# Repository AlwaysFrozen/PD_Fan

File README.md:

# PD_Fan
A USB TYPE_C powered 4-PIN PWM fan controller  
PD decoy was performed with WCH CH224  
Support 5v, 9v, 12v, 15v, 20v fixed pd gear  
Use the WCH CH571 for BLE communication,PWM control and speed measurement

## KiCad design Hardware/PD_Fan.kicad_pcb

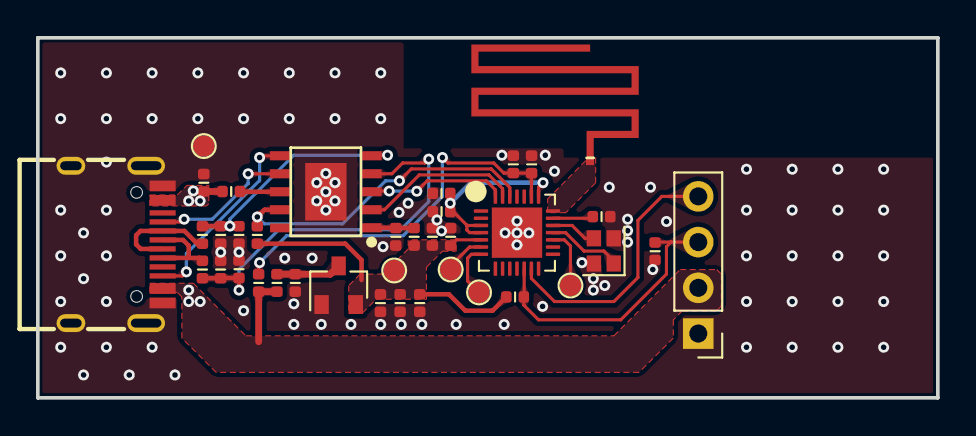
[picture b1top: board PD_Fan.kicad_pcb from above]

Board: 2 copper layers, 50.0 x 20.0 mm, 38 parts (0 on the bottom side), 26 nets.

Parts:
ANT1: Antenna; ANT_AN5129
C1, C2, C4, C5: 10pF/50V; C_0402
C3: 10uF/50V; C_0402
C6, C7: 10uF/6.3V; C_0402
C8, C15: 0.1uF/50V; C_0402
C9: 1uF/10V X7R; C_0402
C10, C11, C13, C14: 2.2uF/6.3V; C_0402
C12: 0.1uF/25V; C_0402
D1, D2: ESD0402TS050D03; C_0402
J1: Conn_01x04_Pin; PinHeader_1x04_P2.54mm_Vertical
J2: TYPE-C; YH-036-013A
R1: 100K; R_0402
R2, R6, R7, R8: 10K; R_0402
R3, R4, R5: 10R; R_0402
R9: 47R; R_0402
TP1: 3.3V; TestPoint_1.2mm
TP2: GND; TestPoint_1.2mm
TP3: RX; TestPoint_1.2mm
TP4: TX; TestPoint_1.2mm
TP5: BOOT; TestPoint_1.2mm
U1: ME6203A33M3G; SOT-23
U2: CH224K; ESSOP10
U3: CH571F; QFN-28-1EP_4x4mm_P0.4mm_EP2.8x2.8mm
Y1: 32MHz; Crystal_SMD_2016-4Pin_2.0x1.6mm

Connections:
3.3V: C6.2, C7.2, C8.2, C10.2, C12.2, R6.1, R8.1, R9.1, TP1.1, U1.2 (VOUT), U3.5 (VIO33/VDD3)
/ANT: ANT1.1 (A), U3.21 (ANT)
/C-USBDM: C5.2, D2.2 (A2), R5.2, U2.5 (DM)
/C-USBDP: C4.1, D1.1 (A1), R4.2, U2.4 (DP)
/CFG1: R8.2, U2.9 (CFG1), U3.26 (PA14/MOSI/TXD0_/AIN4)
/CFG2: U2.2 (CFG2), U3.27 (PA13/SCK0/AIN3)
/CFG3: U2.3 (CFG3), U3.28 (PA12/SCS/AIN2)
/Control: J1.4, U3.13 (PB10/UD-/TMR1_)
/Sense: C15.2, J1.3, R6.2, U3.12 (PB11/UD+/TMR2_)
/VIN_DET: C2.2, R1.2, R2.1, U3.23 (PA4/AIN0)
GND: C1.1, C2.1, C3.1, C4.2, C5.1, C6.1, C7.1, C8.1, C9.1, C10.1, C11.1, C12.1, C13.1, C14.1, C15.1, D1.2 (A2), D2.1 (A1), J1.1, J2.A1 (GND), J2.A12 (GND), J2.B1 (GND), J2.B12 (GND), J2.S1 (SHIELD), R2.2, TP2.1, U1.1 (VSS), U2.11 (GND), U3.29 (GND), Y1.2, Y1.4
unnamed: J2.A5 (CC1), U2.7 (CC1)
unnamed: J2.B5 (CC2), U2.6 (CC2)
unnamed: J2.A6 (D+), J2.B6 (D+), R4.1
unnamed: J2.A7 (D-), J2.B7 (D-), R5.1
unnamed: C3.2, R3.2, U1.3 (VIN)
unnamed: R7.1, U2.8 (VBUS)
unnamed: C9.2, R9.2, U2.1 (VDD)
unnamed: TP3.1, U3.6 (PA8/RXD1)
unnamed: TP4.1, U3.7 (PA9/TMR0/TXD1)
unnamed: TP5.1, U3.17 (PB22/TMR3)
unnamed: C13.2, C14.2, U3.3 (VDCID), U3.4 (VSW), U3.22 (VDCIA)
unnamed: C11.2, U3.20 (VINTA)
unnamed: U3.19 (X32MI), Y1.3
unnamed: U3.18 (X32MO), Y1.1
USB-VIN: C1.2, J1.2, J2.A4 (VBUS), J2.A9 (VBUS), J2.B4 (VBUS), J2.B9 (VBUS), R1.1, R3.1, R7.2

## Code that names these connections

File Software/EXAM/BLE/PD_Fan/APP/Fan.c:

#include "CONFIG.h"
#include "Fan.h"

/*
    CH224 voltage set
    CFG1    CFG2    CFG3
    1       -       -       5v
    0       0       0       9v
    0       0       1       12v
    0       1       1       15v
    0       1       0       20v
*/

#define CFG1_PIN    GPIO_Pin_14
#define CFG2_PIN    GPIO_Pin_13
#define CFG3_PIN    GPIO_Pin_12

#define CFG1_H      GPIOA_SetBits(CFG1_PIN)
#define CFG1_L      GPIOA_ResetBits(CFG1_PIN)
#define CFG2_H      GPIOA_SetBits(CFG2_PIN)
#define CFG2_L      GPIOA_ResetBits(CFG2_PIN)
#define CFG3_H      GPIOA_SetBits(CFG3_PIN)
#define CFG3_L      GPIOA_ResetBits(CFG3_PIN)

#define PWM_FREQ    (25000)
#define PWM_CYCLE   (60000000 / PWM_FREQ)

static uint8_t pd_target_vol = 5;
static uint8_t fan_target_duty = 0;
static uint16_t RPM = 0;

void PD_Init(void)
{
    GPIOA_ModeCfg(GPIO_Pin_0,GPIO_ModeIN_Floating);
    ADC_ExtSingleChSampInit( SampleFreq_3_2, ADC_PGA_0 );

    CFG1_H;
    CFG2_L;
    CFG3_L;
    GPIOA_ModeCfg(CFG1_PIN | CFG2_PIN | CFG3_PIN,GPIO_ModeOut_PP_5mA);
}

void Set_PD_Vol(uint8_t vol)
{
    pd_target_vol = vol;

    switch(vol)
    {
        case 5:
            CFG1_H;
            CFG2_L;
            CFG3_L;
            break;

        case 9:
            CFG1_L;
            CFG2_L;
            CFG3_L;
            break;

        case 12:
            CFG1_L;
            CFG2_L;
            CFG3_H;
            break;

        case 15:
            CFG1_L;
            CFG2_H;
            CFG3_H;
            break;

        case 20:
            CFG1_L;
            CFG2_H;
            CFG3_L;
            break;

        default:
            break;
    }
}

uint8_t Get_PD_Vol(void)
{
    return pd_target_vol;
}

uint16_t Get_VBUS_Vol(void)
{
    uint16_t adc[2];
    uint16_t vol;

    ADC_ChannelCfg(0);
    ADC_ExcutSingleConver();
    adc[0] = ADC_ExcutSingleConver();
    adc[1] = ADC_ExcutSingleConver();
    // vol = (adc[0] + adc[1]) / 2 / 4095 * 2100 * ((100 + 10) / 10) ;
    vol = (adc[0] + adc[1]) * 2.8205128f;

    return vol;
}

void Fan_Init(void)
{
    GPIOPinRemap(ENABLE, RB_PIN_TMR1);
    GPIOPinRemap(ENABLE, RB_PIN_TMR2);
    GPIOB_ModeCfg(GPIO_Pin_10, GPIO_ModeOut_PP_20mA);
    GPIOB_ModeCfg(GPIO_Pin_11, GPIO_ModeIN_Floating);

    TMR1_PWMInit(High_Level, PWM_Times_1);
    TMR1_PWMCycleCfg(PWM_CYCLE);
    TMR1_Disable();
    TMR1_PWMActDataWidth(0);
    TMR1_Enable();

    TMR2_EXTSingleCounterInit(FallEdge_To_FallEdge);
    TMR2_CountOverflowCfg(0xfffffd);
}

void Set_Fan_Duty(uint8_t duty)
{
    fan_target_duty = duty;

    TMR1_PWMActDataWidth(PWM_CYCLE * duty / 100);
}

uint8_t Get_Fan_Duty(void)
{
    return fan_target_duty;
}

void Cal_Fan_RPM(uint32_t time_ms)
{
    uint16_t pulse_cnt = 0;

    pulse_cnt = TMR2_GetCurrentCount();
    //  clear count register
    TMR2_CountOverflowCfg(0xfffffd);

    RPM = pulse_cnt * 60000 / time_ms / 2;

    // PRINT("Cal_Fan_RPM %d %d\n",RPM,pulse_cnt);
}

uint16_t Get_Fan_RPM(void)
{
    return RPM;
}

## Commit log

2023-09-28 Add hardware data
2023-10-07 commit software
